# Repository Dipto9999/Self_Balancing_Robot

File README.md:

# WALL-E (Self Balancing Robot)

## Contents

* [Overview](#overview)
  * [Features](#features)
  * [Components](#components)
* [System Design](#system-design)
  * [Functional Diagram](#functional-diagram)
  * [Architecture Diagram](#architecture-diagram)
* [Robot Firmware](#robot-firmware)
  * [Arduino](#arduino)
  * [STM32](#stm32)
* [User Software](#user-software)
  * [Driver App](#driver-app)
  * [Dashboard App](#dashboard-app)
* [Demonstration](#demonstration)
* [Credit](#credit)

---

## Overview

We designed **WALL-E**, an autonomously balancing two-wheel robot driven wirelessly via Bluetooth.

### Features

WALL-E prioritizes safe navigation and secure access.

- Detects the nearby environment (i.e. obstacles, color recognition)
- Prevents unauthorized control with **RFID** authentication and BLE pairing code.
- Generates live camera feed and uploads to **AWS S3** cloud storage.

### Components

- **Microcontrollers**:
  - Arduino Nano 33 BLE Sense Rev2 (Balancing & BLE)
  - STM32L051K8T6 (Environmental Sensors, Auth)
  - Raspberry Pi Zero 2 W (Camera Feed)

- **Sensors and Modules**:
  - BMM150 IMU
  - HC-SR04 Ultrasonic Distance Sensor
  - TCS34725 Color Sensor
  - RC522 RFID Module
  - CEM-1302 Buzzer
  - Freenove 5MP Camera

- **Actuation**:
  - DRV8833 Motor Drivers
  - Pololu 37D DC Motors

---

## System Design

### Functional Diagram

### Architecture Diagram

---

## Robot Firmware

### Arduino

- Autonomously balances robot with closed-loop control system (i.e. PID controller).
- Uses complementary filter to measure angular input from accelerometer and gyroscope sensors.
- Drives motors by generating PWM (slow decay) output to DRV8833 chip.
- Uses statemachine to prioritize balancing / movement functionality.
    - Injects noise (i.e. angular offset, PWM signals) to induce movement along axis / turning.

<p align="center">
  <i>
    Source Code in <a href="/Arduino_Firmware/main">Arduino_Firmware</a> directory.
  </i>
</p>

### STM32

- Handles auxiliary features to reduce computational load on Arduino.
    - **Distance Sensing**: Toggles GPIO signal-low when object detected within 30cm.
    - **Color Detection**: Toggles GPIO signal-low when red is detected. WALL-E avoids red-lights at all costs.
    - **RFID Authentication**: Verifies UID and signals Arduino on success.
    - **Buzzer**: Alerts user on successful auth, errors, or warnings via PWM tone generation.

<p align="center">
  <i>
    Source Code in <a href="/STM32_Firmware">STM32_Firmware</a> directory.
  </i>
</p>

## User Software

### Robot Driver App

- **Flask** web application hosted via **ngrok** for mobile access
- Uses **GET**/**POST** requests to update server with **UI** updates and perform Bluetooth operations.
- Handles **BLE** pairing authentication in backend (i.e. without affecting user experience).

<p align="center">
  <i>
    Source Code in <a href="/Driver_App">Driver_App</a> directory.
  </i>
</p>

### Dashboard App

- **Python** application with live camera stream on **Tkinter GUI**.
    - Camera runs at ~20 FPS with reduced resolution for performance on Pi Zero 2 W.
- Snapshot and recording functionality with automatic upload to **AWS S3** bucket.

<p align="center">
  <i>
    Source Code in <a href="/Dashboard_App">Dashboard_App</a> directory.
  </i>
</p>

---

## Demonstration

Watch our final robot demonstration here:
📽️ [YouTube Demo](https://youtu.be/UMmxqQl_EAc?si=lTu5z8PBC82dAWoi)

## Report

Read our final project report here:
📝 [Project Report](/Report/ELEC391_B17_ProjectReport.pdf)

## Credit

This was completed as part of the **ELEC 391 - Design Studio** project course in **The University of British Columbia Electrical and Computer Engineering** undergraduate program.

**Team B-17**
- Muntakim Rahman
- Tomaz Zlindra
- Xianyao Li

Special thanks to **Dr. Joseph Yan** for tremendous support and guidance.

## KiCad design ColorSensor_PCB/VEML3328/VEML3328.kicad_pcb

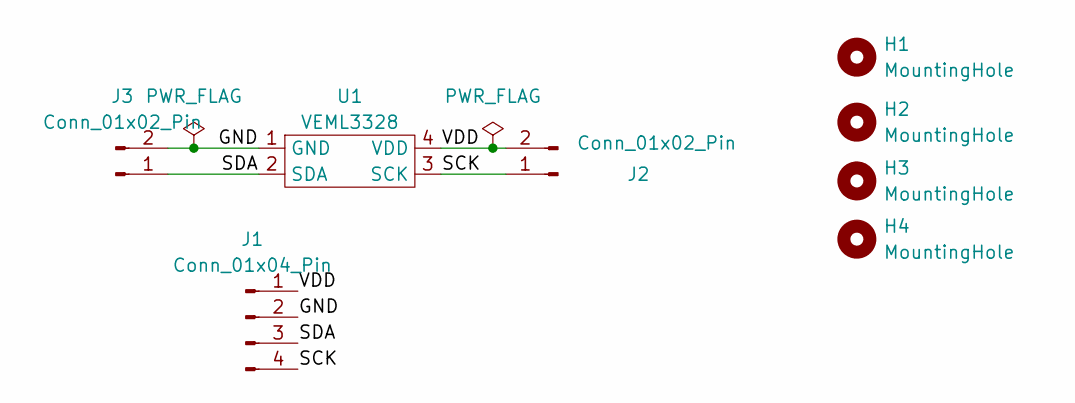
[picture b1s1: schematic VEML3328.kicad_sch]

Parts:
H1, H2, H3, H4: MountingHole; MountingHole_3.2mm_M3
J1: Conn_01x04_Pin; PinHeader_1x04_P2.54mm_Vertical
J2, J3: Conn_01x02_Pin; PinHeader_1x02_P2.54mm_Vertical
U1: VEML3328

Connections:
/GND: J1.2, J3.2 (Pin_1), U1.1 (GND)
/SCK: J1.4, J2.1, U1.3 (SCK)
/SDA: J1.3, J3.1 (Pin_2), U1.2 (SDA)
/VDD: J1.1, J2.2, U1.4 (VDD)

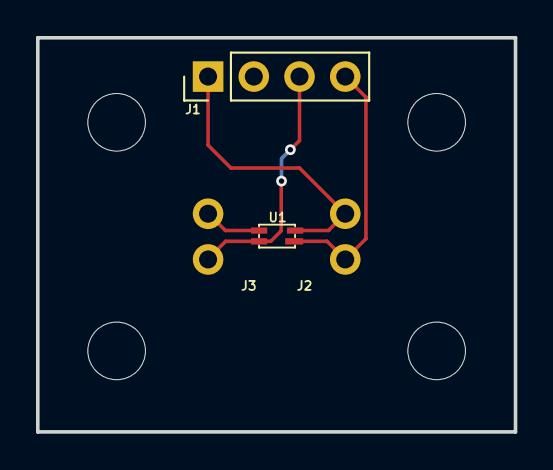
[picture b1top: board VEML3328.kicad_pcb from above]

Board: 2 copper layers, 26.5 x 21.9 mm, 8 parts (0 on the bottom side), 4 nets.

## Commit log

2025-01-28 Compiling so I am Committing
2025-01-28 Angle Calculation Functional
2025-01-28 PWM is partially PWMing. Using mbed OS.
    Something weird with frequency.
2025-01-29 PWM is PWMing with 20 µs
2025-02-07 Functions for PWM
2025-02-10 All Directions Working, But One Wheel Slower RPM.
    ToDo: Test Decay, Test Angle Dependency, Integrate BLE
2025-02-10 Switched AIN, BIN by Board
2025-02-10 Cleaned up Code with Motor Pin Structs and General PWM UDF
2025-02-10 Angles Being Measured, But Not Sure if Accurate
2025-02-10 Fixed Angle Bug -> Had Unintentionally Commented Out Angle Assignments
2025-02-10 Angle Dependent PWM Adjustment
2025-02-10 Completed PWM, Angles (Excluding Accurate Movement Response, PWM to RPM Calibration)
2025-02-10 To Test Tomorrow
2025-02-10 Testing BLE
2025-02-11 BLE Functioning, PWM Functioning, Angle Correct Calculation, Need to Develop App and Understand how to Measure Rotations with Hall Sensor. Also Build Floor 2
2025-02-11 BLE Used to Control!
2025-02-11 Updated Commands and Customized App
2025-02-11 Dashboard Page is Causing Blocking Issues with Latency for BLE
2025-02-11 Need to Implement Firmware for Ensuring Data Transferred Once BLE Connection Established or Prevent Serial Until Established
2025-02-11 It Seems We Must Wait to Transmit Angle Data After BLE Connection Established
2025-02-12 End of Day 2025-02-11
    BLE and Serial Not Cooperating
    Got ~29%, 50%, 75%, 100% RPM (Minimum With Current is 29%)
    Robot Built
2025-02-12 Added Hall Sensor Measurement Rig STM Project
2025-02-13 End of Day 2025-02-12
    Functioning BLE - UART (Issue was with Firmware Forever Loop)
    Ready for Proof of Concept Demo
2025-02-13 Updated gitignore
2025-02-13 Using venv for Raspberry Pi
2025-02-13 Updated Directories, Requirements
2025-02-24 stm most features done
2025-02-25 Added PWM BoilerPlate Code. Need to Test (i.e. Time Works, Angle Measured, Receiving BLE Commands, Etc. -> Integration Test)
2025-02-27 PID Does Not Appear to Have Broken Any Functionality
2025-02-27 Tested dt Change
2025-02-27 Measured dt in Between Measurements
2025-02-27 Measured dt (Time Between Measurements)
2025-02-27 Distance Sensor Works
2025-02-27 Removing Unnecessary Files for Pi
2025-03-02 Transferring to Raspberry Pi (Test Camera Placement)
2025-03-02 Testing Camera Integration on Pi
2025-03-03 Testing Camera Sizing
2025-03-03 Trying to Change Pi Camera Window Size
2025-03-03 Updating with Changes from main, Raspberry_Pi
2025-03-03 Saving Camera Recordings
2025-03-03 Saving to Output File
2025-03-03 Testing Camera Recording
2025-03-03 Ignoring Large Media for Now
2025-03-03 Convert Pi Video to MP4
2025-03-03 Testing Clock Scheduling for Video Outputs
2025-03-03 Trying to Convert Video to MP4
2025-03-03 Adding Test File for Debugging
2025-03-03 Test Script Working
2025-03-03 Testing MP4 Integration
2025-03-03 Updating Filepath Logic
2025-03-03 Testing On Close Functionality
2025-03-03 Saving Video, Attempting to Close App Before Conversion
2025-03-03 Attempting to Use Separate Process
2025-03-03 Making Ticks Smaller
2025-03-03 Trying to Shutdown Separately
2025-03-03 Trying to Detach Process
2025-03-03 Trying to Detach and Run Process
2025-03-04 Trying to Give it Time to Start
2025-03-04 Testing Video Processing
2025-03-04 Updating Driver App
2025-03-04 Try to Update Bleak Client Adapter
2025-03-04 Speaker Code, fixed small issues with distance sensor code, all for G0
2025-03-04 Flask Code Generated
2025-03-05 Updated App
2025-03-05 Testing Mobile Responsiveness
2025-03-05 Updated Styling
2025-03-05 Going to Rework and Replace Dashboard App
2025-03-05 Restructuring Dashboard App
2025-03-05 Testing on Pi
2025-03-05 Updated venv
2025-03-05 Test Button Functionality
2025-03-05 Testing Convert and Flip Functionality
2025-03-05 Test File Conversion on Pi 4
2025-03-05 Found missing import
2025-03-05 Testing Why App Freaked Out
2025-03-05 Testing Again to See Why Freaked Out
2025-03-05 Testing Camera Open/Close on Pi 4
2025-03-05 New Logic for Sample Time. Test and Update Angle Bounds
2025-03-06 ToDo: Test Withou 180 Degree Offset
2025-03-06 Test Out Video Conversion
2025-03-06 Found Why Freaking Out
2025-03-06 Fixing All Stale References
2025-03-06 Stale Reference Fixes
2025-03-06 Attempting to Convert Videos With Removal of all h264 streams
2025-03-06 Testing App Record/Stop
2025-03-06 Trying to Stop and Restart, With Snapshot Feature
2025-03-06 Trying to Test Camera Without Annoying Logs
2025-03-06 Updating Video Converter to Be Separate Script
2025-03-06 Test Camera With New Config
2025-03-06 Testing Camera With Config
2025-03-06 Testing Conversion
2025-03-06 Testing No Logging
2025-03-06 Test Out App Without Multiprocessing
2025-03-06 Trying to Join Threads
2025-03-06 Adding Dashboard App with Camera Features
2025-03-06 Adding Dashboard App
2025-03-06 Getting Rid of Venv for Main Branch (Slow and Too Many Diffs)
2025-03-06 Starting off with Kp = 0.6, Ki = 0, Kd = 0
2025-03-06 RFID complete, some new Speaker methods, still need to complete speaker firmware with RFID
2025-03-06 New Kp, Kd for Testing
2025-03-11 Updated to Slow Decay
2025-03-11 PID tuning 3/11/2025
2025-03-12 speaker with rfid
2025-03-12 Working on STM32_Integration
2025-03-12 Testing for Toggle Pin
2025-03-12 GPIO to Arduino
2025-03-13 Testing Interrupt
2025-03-13 Testing ISR
2025-03-13 Testing
2025-03-13 Trying to Integrate ISR
2025-03-13 Trying to Integrate ISR. Working with Current Files. Add Rest of Firmware
2025-03-13 BLE Test Working
2025-03-13 Seems to Be Working with PWM
2025-03-13 Functioning With Angle Import
2025-03-13 Angle Test Functioning
2025-03-13 Working with Final Import. Now to Call Functions
2025-03-13 ISR Is Integrated
2025-03-13 speaker only toggling if bot enabled
2025-03-15 ISR Functioning at 100 ms
2025-03-15 ISR Integrated, STM32 RFID Pin Added (Using for ISR Testing Right Now)
2025-03-16 Running at 20 Hz
2025-03-16 Applying and Testing PWM with ISR
2025-03-16 Updating for MATLAB Model. Running ISR at 50 Hz
2025-03-17 Testing Tkinter on Raspberry Pi
2025-03-17 accidentally put stm32 code on raspberrypi_uart branch
2025-03-18 Testing New Camera Code
2025-03-18 Try to Implement via Tkinter
2025-03-18 Testing Out Camera
2025-03-18 Testing Camera
2025-03-18 Testing Camera App
2025-03-18 Testing Cam
2025-03-18 Testing Refresh Rate
2025-03-18 Testing Refresh
2025-03-18 Testing in main.py
2025-03-18 Testing App
2025-03-18 Testing Without Stripchart
2025-03-19 some shit aint working
2025-03-19 End of Day 2025-03-18
2025-03-19 Trying to Run Stripchart and Camera
2025-03-19 Testing App Reconfig
2025-03-19 Testing Update to Tk.Frame
2025-03-19 Testing Stripchart and Camera
2025-03-19 Testing Dashboard
2025-03-19 Test Update Feed
2025-03-19 Test on Raspberry Pi
2025-03-19 Updated for Test
2025-03-19 Testing Cam Feed
2025-03-19 Replaced App
2025-03-19 Testing Camera Frame
2025-03-19 Testing Snapshot
2025-03-19 Testing Camera Snapshot
2025-03-19 Testing Kp, Kd Values
2025-03-19 Testing Kp, Kd Valuies
2025-03-19 Color Sensor not working, but otherwise everything else should work
2025-03-20 End of Day 2025-03-19
2025-03-20 Commit and Merge this Shit
2025-03-20 Ki 1.75 Seems Like Max Without Overshoot
2025-03-20 initial skeleton code, not tested
2025-03-20 Ready for Driver Development
2025-03-20 Testing, Going to Temporarily Increase Ki
2025-03-21 Updated Ki Condition
2025-03-21 Trying to Address Racing Issue
2025-03-21 Need to Improve IMU Sample Rate
2025-03-21 Updated to Include X Button
2025-03-22 End of Day 2025-03-21
2025-03-22 Testing App Config
2025-03-22 Update App Config
2025-03-22 Wrong Button Config
2025-03-22 Testing UART
2025-03-23 Added Serial Test
2025-03-23 Testing Serial
2025-03-23 Test with This
2025-03-23 BLE At Low Frequency
2025-03-24 End of Day 2025-03-23
2025-03-24 BLE Has Been Reintegrated
2025-03-24 Committing and Merging PID
2025-03-25 trying to tune PID
2025-03-25 Integrating Polling BLE
2025-03-25 a few minor PID changes
2025-03-25 Trying New Update
2025-03-25 Testing Out 500 ms
2025-03-25 Updating Serial Stripchart to 1s, 25 Data Size. Need to Test
2025-03-25 Happy With Serial Updates
2025-03-27 Fixed Stripchart for Desktop Envt. Need to Test on Pi
2025-03-27 Testing Resize
2025-03-27 Testing Frame Sizes
2025-03-27 Cannot Find Button Frames
2025-03-27 Testing Config
2025-03-27 Testing Layout
2025-03-27 small changes
2025-03-27 PID Testing
2025-03-27 Leon Testing
2025-03-28 Removing Complexities
2025-03-28 Bug with Kp, Ki, Kd Assignments
2025-03-28 Movement Partially Done
2025-03-28 colorsensor working
2025-03-29 IT IS BALANCING
2025-03-30 Test Setpoint Angle 0.0
2025-03-30 Final Tweaking
2025-03-30 Adding Back Movement Logic for Testing
2025-03-30 Configuration with Batteries
2025-04-01 Init 2025-04-01
2025-04-01 did update on stm32cubeIDE
2025-04-02 Testing Movement Finally
2025-04-02 Testing 6:12 Leaving Lab
2025-04-03 Movement is Ok. Need to Integrate STM32
2025-04-03 Get 1s Data
2025-04-03 Ready for STM32 Integration
2025-04-04 Movement and STM32 Integrated. Need to Tweak Balancing and Movement
2025-04-04 color sensor commented out
2025-04-05 errorAccumulation accumulates forever, but now balances
2025-04-05 Test Camera App. Fix Issues with Stripchart App
2025-04-05 Test Camera App. Need to Fix Issues with Stripchart App
2025-04-05 Testing Camera Stop
2025-04-05 Testing Alternate App
2025-04-05 Movement Being Tweaked
2025-04-05 Tweaked Movement. Will Test for Ramp
2025-04-06 BLE Password Implemented
2025-04-06 Trying to Fix Data Logging and Display for Pi Stripchart
2025-04-06 Getting Rid of Redundant Comments
2025-04-06 Added new GPIO to Arduino with Colorsensor
2025-04-06 Added Pin Adjustment
2025-04-06 Adding Red Alert. Need to Fully Integrate
2025-04-06 Updated the Pins
2025-04-07 Ready to Merge
2025-04-07 Stripchart Works on Windows. Need to Test on Pi
2025-04-07 stuff
2025-04-07 WALL-E
2025-04-07 Tweaked for Demo. Setpoint Angle 0.3
2025-04-08 Demo Code
2025-04-08 Added Raspberry Pi App + S3 Code
2025-04-09 Testing README Deployment
2025-04-10 Added MATLAB & Simulink model
2025-04-10 Getting Rid of Redundant Stripchart
2025-04-11 Updated Report, Diagrams
2025-04-11 Updated Report
2025-04-14 updated intro/conclusion, reference for the report & misc.
2025-04-14 Manually Addressing Report Diffs
2025-04-14 Updated Main
2025-04-14 Updating Report
2025-04-14 Updated Headers
2025-04-14 Final Review
2025-04-14 Complete Report!
2025-04-14 Final Report
2025-04-14 Submit Report
2025-04-14 Ready for Github
2025-04-14 Testing README Changes
2025-04-15 Removing Unused Vars, Fixing Cmd App with Lock Screen, Working on Fixing Stripchart Delay
2025-04-15 Using CPP Files for Better Compiling Speed
2025-04-15 Updated DesktopApp. Need to Add Passcode and Text Entry to WebApp
2025-04-15 Testing README
2025-04-15 Updated Connection Button, Text Entry. Need to Add Password
2025-04-15 Login Page Implemented
2025-04-15 Added Logout Button
2025-04-16 Fixed Sizing for Iphone, Ipad, Desktop
2025-04-16 Added Requirements
2025-04-16 Deploying with Render
2025-04-16 Use ngrok. BLE Can't Be Detected from Server
2025-04-16 Fixed ScanButton Bug in Driver App. Stripchart is Perfect on Desktop. Need to Fix for Raspberry Pi
2025-04-16 Testing on Raspberry Pi
2025-04-17 Updated Stripchart Save Function
2025-04-17 Adding Serial Test
2025-04-17 Testing Stripchart
2025-04-17 Testing Comms with Pi-Arduino
2025-04-17 Found General Issue:
    Raspberry Pi UART Works With Loopback.
    Arduino Cannot Receive the b'A' Being Sent from Raspberry Pi
2025-04-17 Added Serial Tests
2025-04-17 Test Worked! Will Demo Serial!
2025-04-17 Updating S3.py
2025-04-17 Try to Upload Figures
2025-04-17 Retrieved all S3 Files
